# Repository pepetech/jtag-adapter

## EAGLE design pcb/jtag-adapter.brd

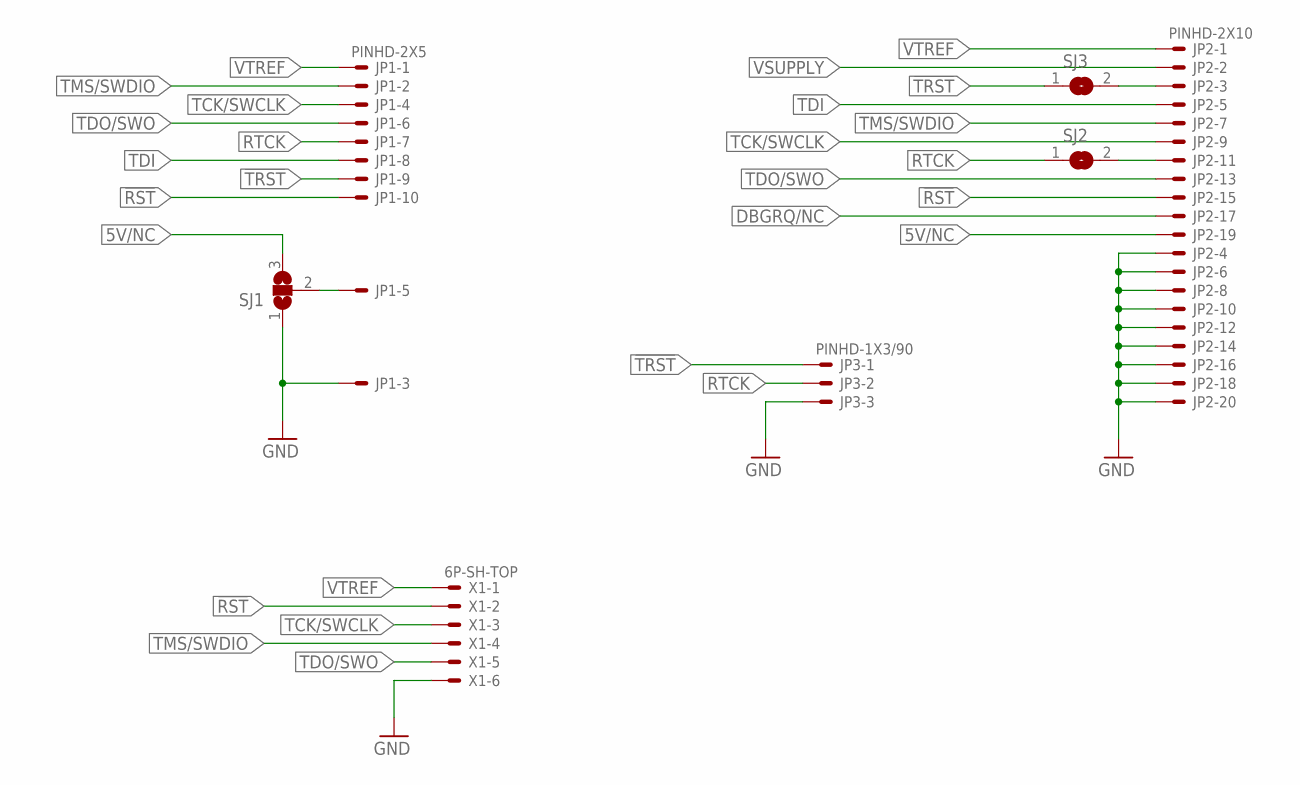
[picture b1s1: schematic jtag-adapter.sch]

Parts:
JP1: PINHD-2X5; 2X05
JP2: PINHD-2X10; 2X10
JP3: PINHD-1X3/90; 1X03/90
SJ1: SJ2S; SJ2_S
SJ2, SJ3: SJS; SJ_S
X1: 6P-SH-TOP; SH-06-TOP

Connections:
5V/NC: JP2.19, SJ1.3
!RST: JP1.10, JP2.15, X1.2
!TRST: JP1.9, JP3.1, SJ3.1
DBGRQ/NC: JP2.17
GND: JP1.3, JP2.4, JP2.6, JP2.8, JP2.10, JP2.12, JP2.14, JP2.16, JP2.18, JP2.20, JP3.3, SJ1.1, X1.6
unnamed: JP2.11, SJ2.2
unnamed: JP1.5, SJ1.2
unnamed: JP2.3, SJ3.2
RTCK: JP1.7, JP3.2, SJ2.1
TCK/SWCLK: JP1.4, JP2.9, X1.3
TDI: JP1.8, JP2.5
TDO/SWO: JP1.6, JP2.13, X1.5
TMS/SWDIO: JP1.2, JP2.7, X1.4
VSUPPLY: JP2.2
VTREF: JP1.1, JP2.1, X1.1

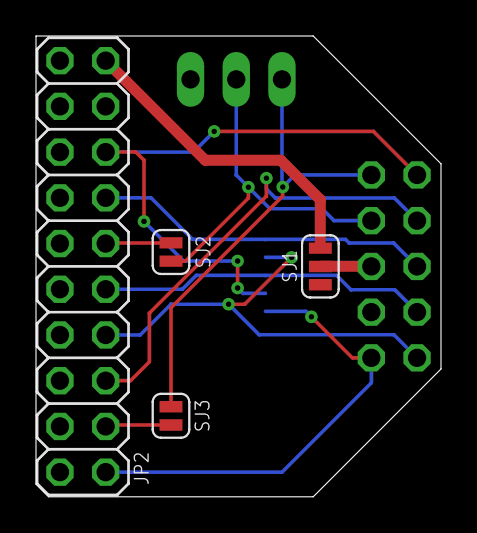
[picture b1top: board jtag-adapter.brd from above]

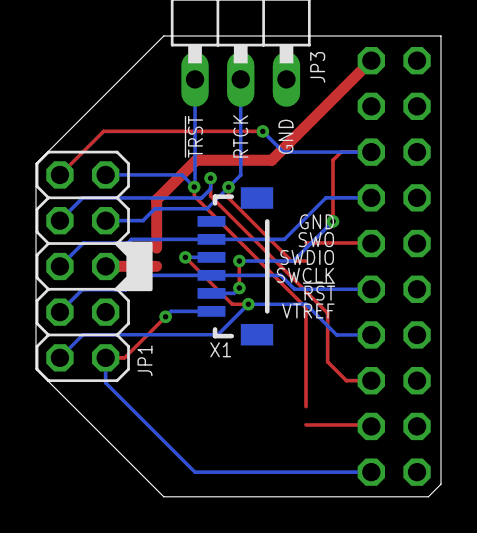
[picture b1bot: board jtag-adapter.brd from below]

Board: 2 copper layers, 22.5 x 25.6 mm, 7 parts (3 on the bottom side), 13 nets.

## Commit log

2019-05-30 Fix thin PCB track
